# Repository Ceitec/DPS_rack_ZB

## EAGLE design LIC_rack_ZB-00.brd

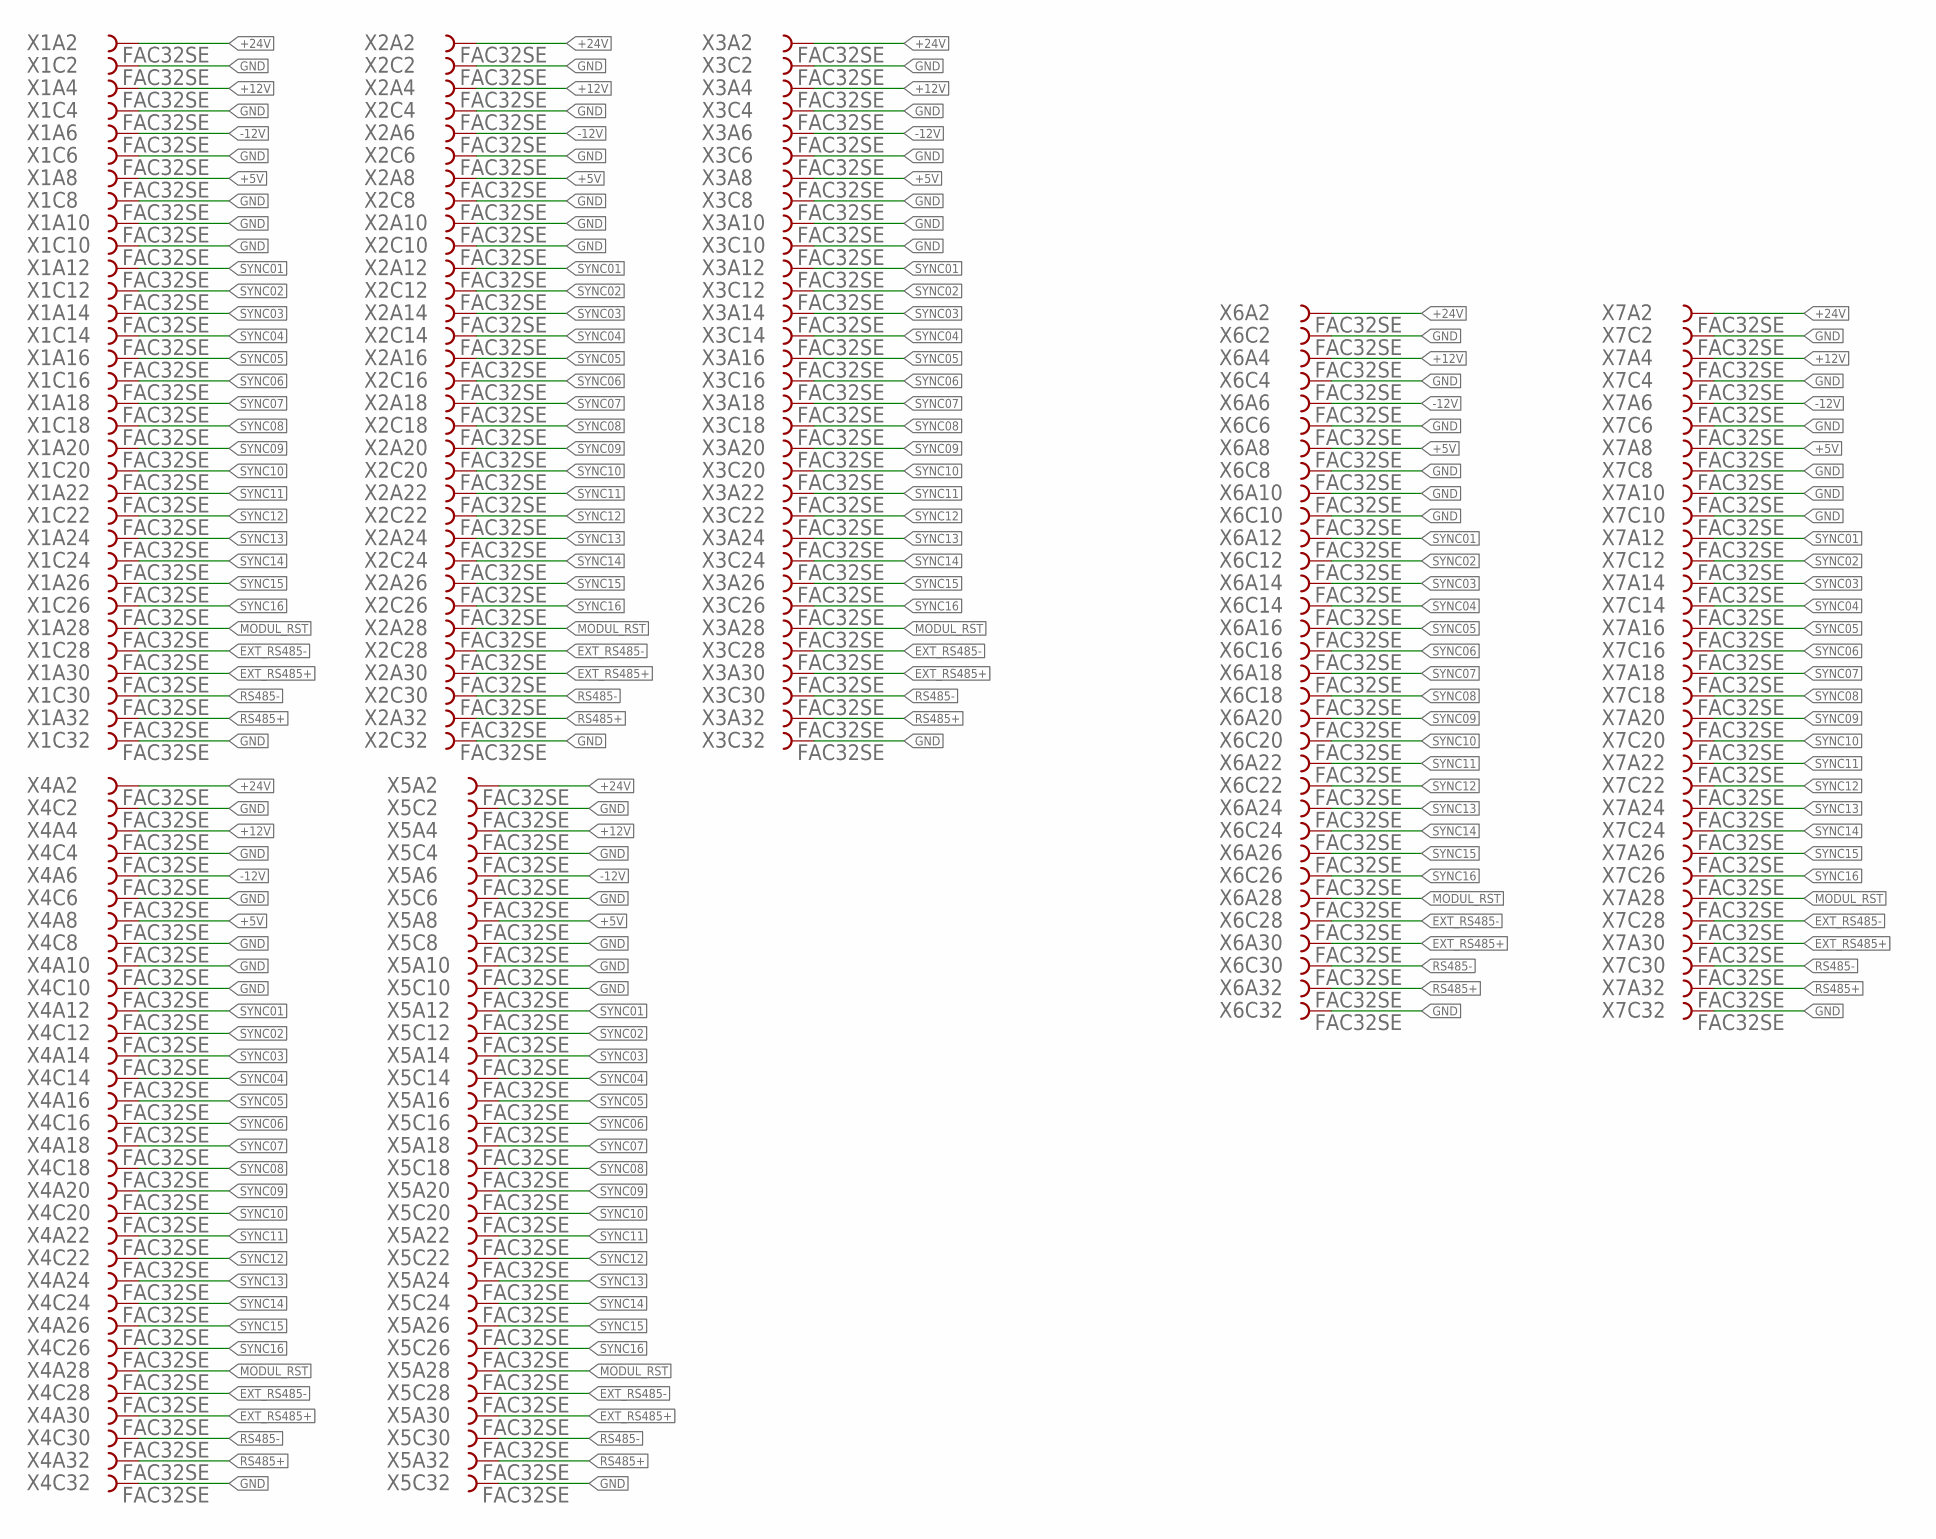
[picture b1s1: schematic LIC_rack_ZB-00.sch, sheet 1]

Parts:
X1, X2, X3, X4, X5, X6, X7: FAC32SE; FAC32S

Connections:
+5V: X1.A8, X2.A8, X3.A8, X4.A8, X5.A8, X6.A8, X7.A8; also elsewhere on the board
+12V: X1.A4, X2.A4, X3.A4, X4.A4, X5.A4, X6.A4, X7.A4; also elsewhere on the board
+24V: X1.A2, X2.A2, X3.A2, X4.A2, X5.A2, X6.A2, X7.A2; also elsewhere on the board
-12V: X1.A6, X2.A6, X3.A6, X4.A6, X5.A6, X6.A6, X7.A6; also elsewhere on the board
EXT_RS485+: X1.A30, X2.A30, X3.A30, X4.A30, X5.A30, X6.A30, X7.A30; also elsewhere on the board
EXT_RS485-: X1.C28, X2.C28, X3.C28, X4.C28, X5.C28, X6.C28, X7.C28; also elsewhere on the board
GND: X1.A10, X1.C2, X1.C4, X1.C6, X1.C8, X1.C10, X1.C32, X2.A10, X2.C2, X2.C4, X2.C6, X2.C8, X2.C10, X2.C32, X3.A10, X3.C2, X3.C4, X3.C6, X3.C8, X3.C10, X3.C32, X4.A10, X4.C2, X4.C4, X4.C6, X4.C8, X4.C10, X4.C32, X5.A10, X5.C2, X5.C4, X5.C6, X5.C8, X5.C10, X5.C32, X6.A10, X6.C2, X6.C4, X6.C6, X6.C8, X6.C10, X6.C32, X7.A10, X7.C2, X7.C4, X7.C6, X7.C8, X7.C10, X7.C32; also elsewhere on the board
MODUL_RST: X1.A28, X2.A28, X3.A28, X4.A28, X5.A28, X6.A28, X7.A28; also elsewhere on the board
RS485+: X1.A32, X2.A32, X3.A32, X4.A32, X5.A32, X6.A32, X7.A32; also elsewhere on the board
RS485-: X1.C30, X2.C30, X3.C30, X4.C30, X5.C30, X6.C30, X7.C30; also elsewhere on the board
SYNC01: X1.A12, X2.A12, X3.A12, X4.A12, X5.A12, X6.A12, X7.A12; also elsewhere on the board
SYNC02: X1.C12, X2.C12, X3.C12, X4.C12, X5.C12, X6.C12, X7.C12; also elsewhere on the board
SYNC03: X1.A14, X2.A14, X3.A14, X4.A14, X5.A14, X6.A14, X7.A14; also elsewhere on the board
SYNC04: X1.C14, X2.C14, X3.C14, X4.C14, X5.C14, X6.C14, X7.C14; also elsewhere on the board
SYNC05: X1.A16, X2.A16, X3.A16, X4.A16, X5.A16, X6.A16, X7.A16; also elsewhere on the board
SYNC06: X1.C16, X2.C16, X3.C16, X4.C16, X5.C16, X6.C16, X7.C16; also elsewhere on the board
SYNC07: X1.A18, X2.A18, X3.A18, X4.A18, X5.A18, X6.A18, X7.A18; also elsewhere on the board
SYNC08: X1.C18, X2.C18, X3.C18, X4.C18, X5.C18, X6.C18, X7.C18; also elsewhere on the board
SYNC09: X1.A20, X2.A20, X3.A20, X4.A20, X5.A20, X6.A20, X7.A20; also elsewhere on the board
SYNC10: X1.C20, X2.C20, X3.C20, X4.C20, X5.C20, X6.C20, X7.C20; also elsewhere on the board
SYNC11: X1.A22, X2.A22, X3.A22, X4.A22, X5.A22, X6.A22, X7.A22; also elsewhere on the board
SYNC12: X1.C22, X2.C22, X3.C22, X4.C22, X5.C22, X6.C22, X7.C22; also elsewhere on the board
SYNC13: X1.A24, X2.A24, X3.A24, X4.A24, X5.A24, X6.A24, X7.A24; also elsewhere on the board
SYNC14: X1.C24, X2.C24, X3.C24, X4.C24, X5.C24, X6.C24, X7.C24; also elsewhere on the board
SYNC15: X1.A26, X2.A26, X3.A26, X4.A26, X5.A26, X6.A26, X7.A26; also elsewhere on the board
SYNC16: X1.C26, X2.C26, X3.C26, X4.C26, X5.C26, X6.C26, X7.C26; also elsewhere on the board

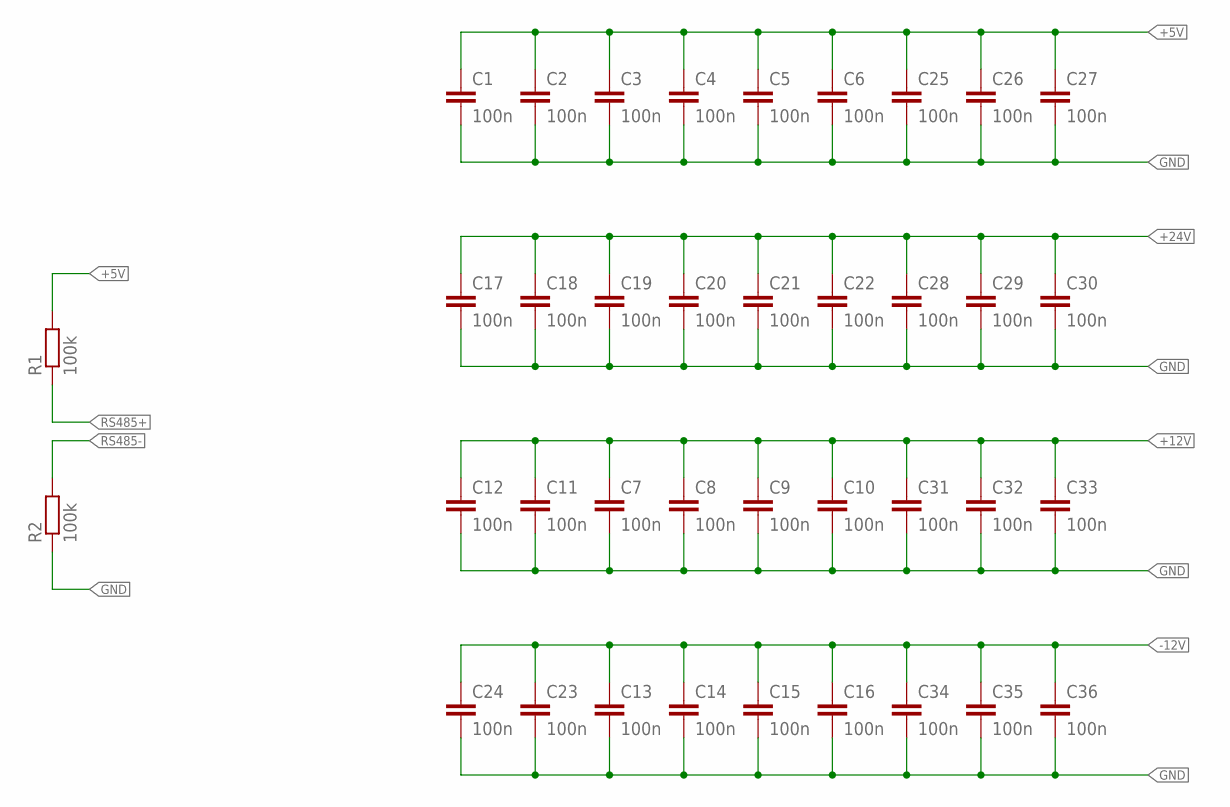
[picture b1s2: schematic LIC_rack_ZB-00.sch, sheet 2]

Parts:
C1, C2, C3, C4, C5, C6, C7, C8, C9, C10, C11, C12, C13, C14, C15, C16, C17, C18, C19, C20, C21, C22, C23, C24, C25, C26, C27, C28, C29, C30, C31, C32, C33, C34, C35, C36: 100n; C1206
R1, R2: 100k; R1206

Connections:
+5V: C1.1, C2.1, C3.1, C4.1, C5.1, C6.1, C25.1, C26.1, C27.1, R1.2; also elsewhere on the board
+12V: C7.1, C8.1, C9.1, C10.1, C11.1, C12.1, C31.1, C32.1, C33.1; also elsewhere on the board
+24V: C17.1, C18.1, C19.1, C20.1, C21.1, C22.1, C28.1, C29.1, C30.1; also elsewhere on the board
-12V: C13.1, C14.1, C15.1, C16.1, C23.1, C24.1, C34.1, C35.1, C36.1; also elsewhere on the board
GND: C1.2, C2.2, C3.2, C4.2, C5.2, C6.2, C7.2, C8.2, C9.2, C10.2, C11.2, C12.2, C13.2, C14.2, C15.2, C16.2, C17.2, C18.2, C19.2, C20.2, C21.2, C22.2, C23.2, C24.2, C25.2, C26.2, C27.2, C28.2, C29.2, C30.2, C31.2, C32.2, C33.2, C34.2, C35.2, C36.2, R2.1; also elsewhere on the board
RS485+: R1.1; also elsewhere on the board
RS485-: R2.2; also elsewhere on the board

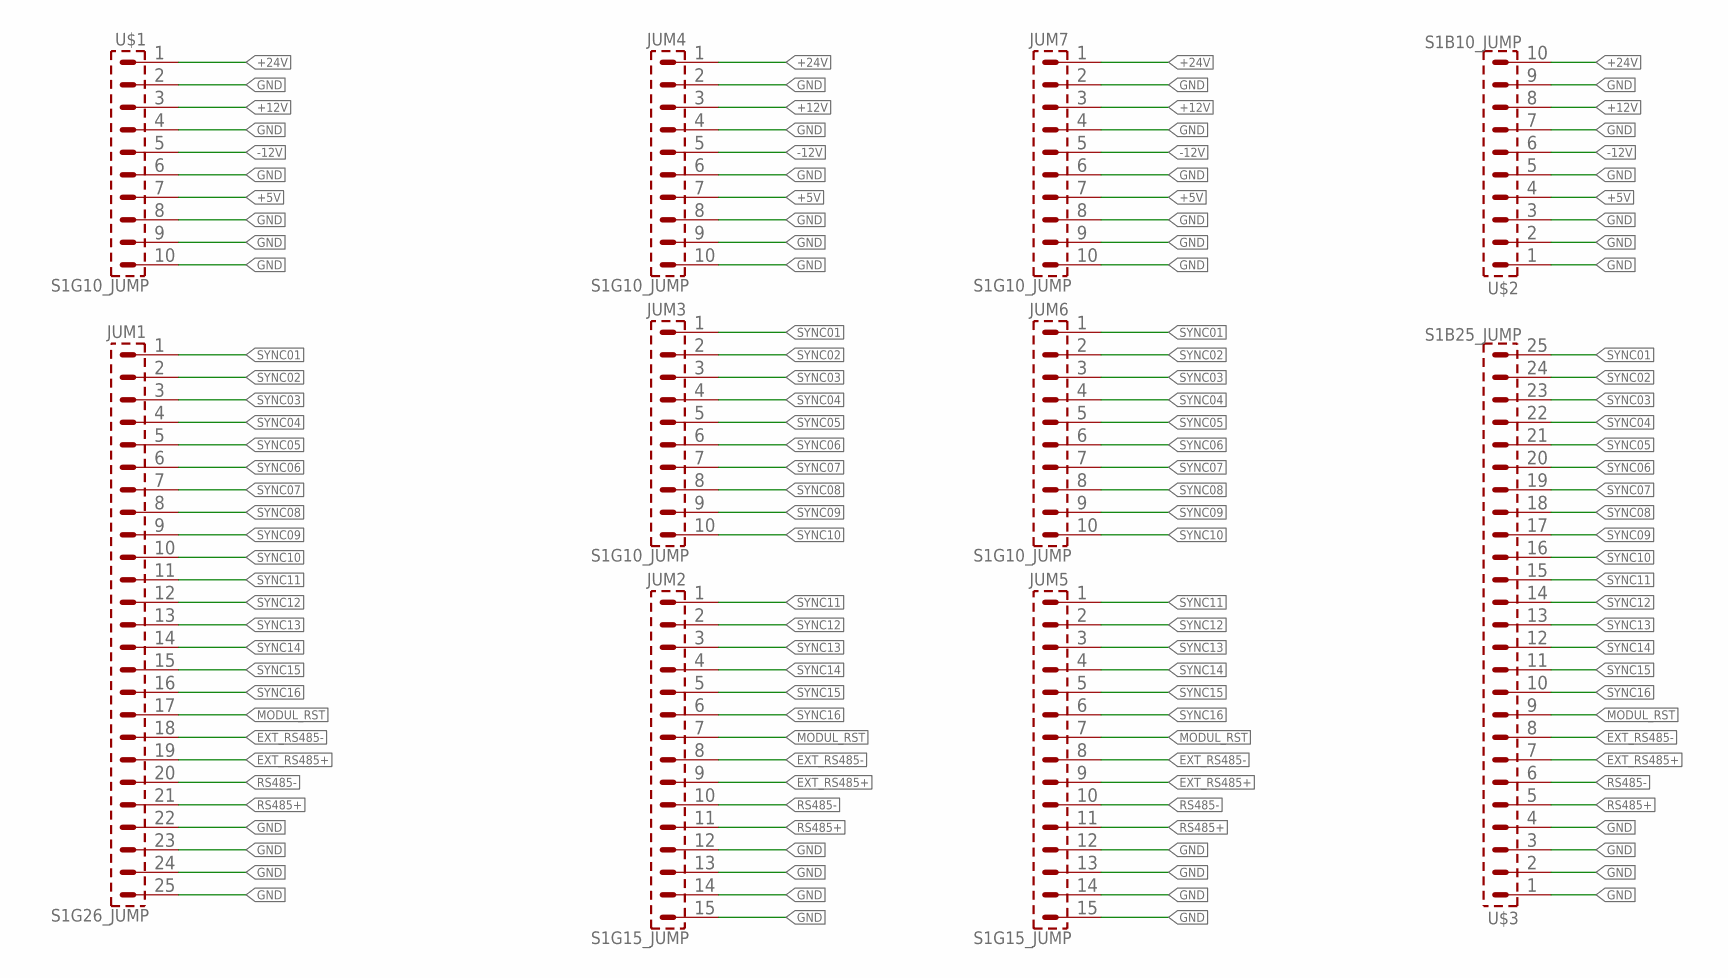
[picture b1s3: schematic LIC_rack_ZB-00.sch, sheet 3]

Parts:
JUM1: S1G26_JUMP; S1G26_JU
JUM2, JUM5: S1G15_JUMP; S1G15_JU
JUM3, JUM4, JUM6, JUM7: S1G10_JUMP; S1G10_JU
U$1: S1G10_JUMP; S1G6_JU
U$2: S1B10_JUMP; S1B10_JU
U$3: S1B25_JUMP; S1B26_JU

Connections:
+5V: JUM4.7, JUM7.7, U$1.7, U$2.4; also elsewhere on the board
+12V: JUM4.3, JUM7.3, U$1.3, U$2.8; also elsewhere on the board
+24V: JUM4.1, JUM7.1, U$1.1, U$2.10; also elsewhere on the board
-12V: JUM4.5, JUM7.5, U$1.5, U$2.6; also elsewhere on the board
EXT_RS485+: JUM1.19, JUM2.9, JUM5.9, U$3.7; also elsewhere on the board
EXT_RS485-: JUM1.18, JUM2.8, JUM5.8, U$3.8; also elsewhere on the board
GND: JUM1.22, JUM1.23, JUM1.24, JUM1.25, JUM2.12, JUM2.13, JUM2.14, JUM2.15, JUM4.2, JUM4.4, JUM4.6, JUM4.8, JUM4.9, JUM4.10, JUM5.12, JUM5.13, JUM5.14, JUM5.15, JUM7.2, JUM7.4, JUM7.6, JUM7.8, JUM7.9, JUM7.10, U$1.2, U$1.4, U$1.6, U$1.8, U$1.9, U$1.10, U$2.1, U$2.2, U$2.3, U$2.5, U$2.7, U$2.9, U$3.1, U$3.2, U$3.3, U$3.4; also elsewhere on the board
MODUL_RST: JUM1.17, JUM2.7, JUM5.7, U$3.9; also elsewhere on the board
RS485+: JUM1.21, JUM2.11, JUM5.11, U$3.5; also elsewhere on the board
RS485-: JUM1.20, JUM2.10, JUM5.10, U$3.6; also elsewhere on the board
SYNC01: JUM1.1, JUM3.1, JUM6.1, U$3.25; also elsewhere on the board
SYNC02: JUM1.2, JUM3.2, JUM6.2, U$3.24; also elsewhere on the board
SYNC03: JUM1.3, JUM3.3, JUM6.3, U$3.23; also elsewhere on the board
SYNC04: JUM1.4, JUM3.4, JUM6.4, U$3.22; also elsewhere on the board
SYNC05: JUM1.5, JUM3.5, JUM6.5, U$3.21; also elsewhere on the board
SYNC06: JUM1.6, JUM3.6, JUM6.6, U$3.20; also elsewhere on the board
SYNC07: JUM1.7, JUM3.7, JUM6.7, U$3.19; also elsewhere on the board
SYNC08: JUM1.8, JUM3.8, JUM6.8, U$3.18; also elsewhere on the board
SYNC09: JUM1.9, JUM3.9, JUM6.9, U$3.17; also elsewhere on the board
SYNC10: JUM1.10, JUM3.10, JUM6.10, U$3.16; also elsewhere on the board
SYNC11: JUM1.11, JUM2.1, JUM5.1, U$3.15; also elsewhere on the board
SYNC12: JUM1.12, JUM2.2, JUM5.2, U$3.14; also elsewhere on the board
SYNC13: JUM1.13, JUM2.3, JUM5.3, U$3.13; also elsewhere on the board
SYNC14: JUM1.14, JUM2.4, JUM5.4, U$3.12; also elsewhere on the board
SYNC15: JUM1.15, JUM2.5, JUM5.5, U$3.11; also elsewhere on the board
SYNC16: JUM1.16, JUM2.6, JUM5.6, U$3.10; also elsewhere on the board

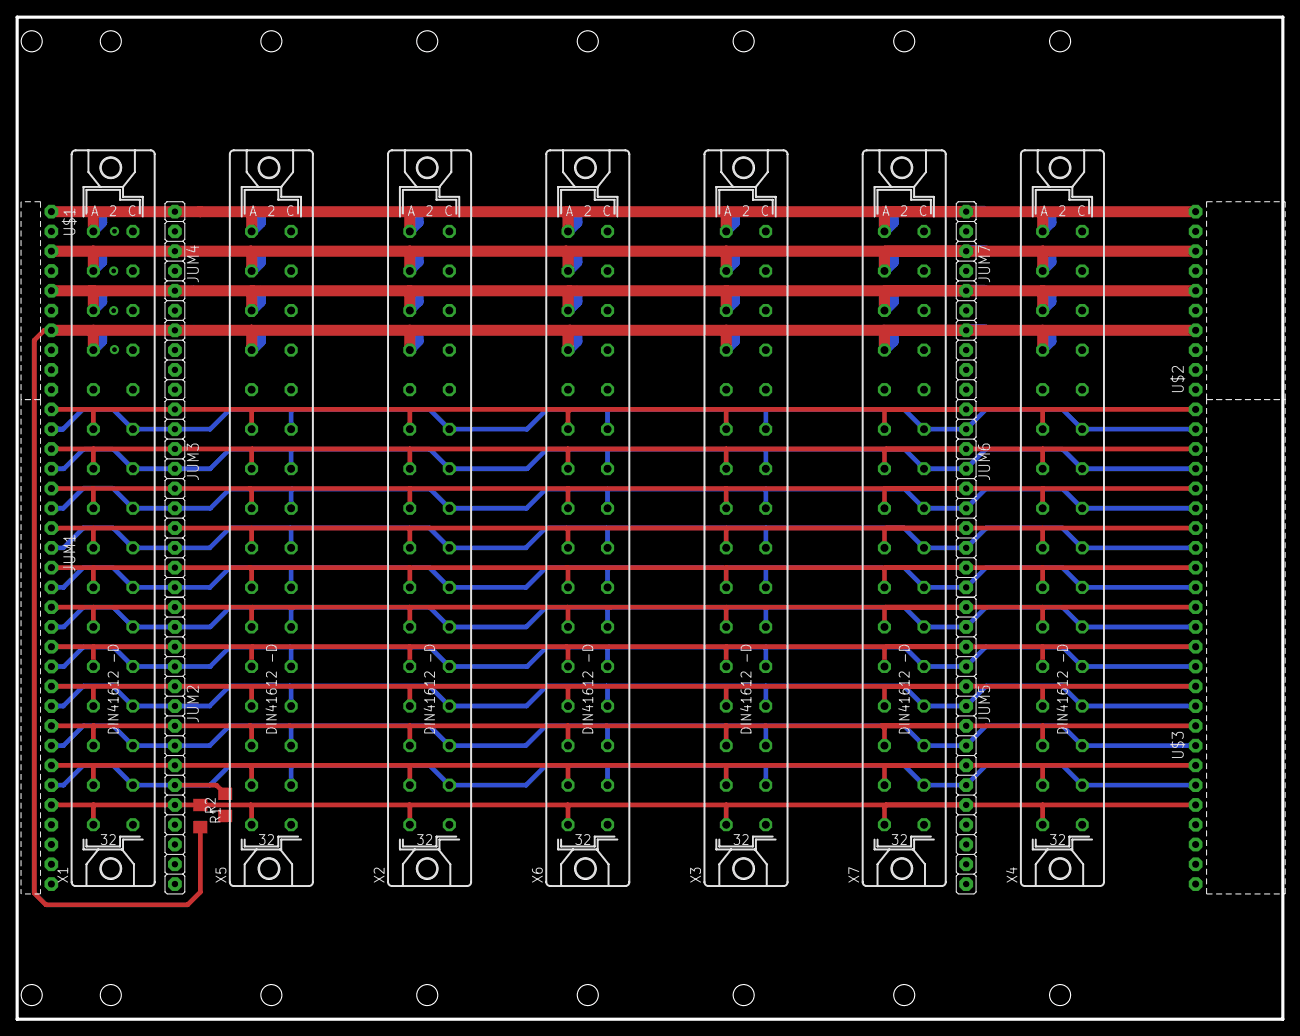
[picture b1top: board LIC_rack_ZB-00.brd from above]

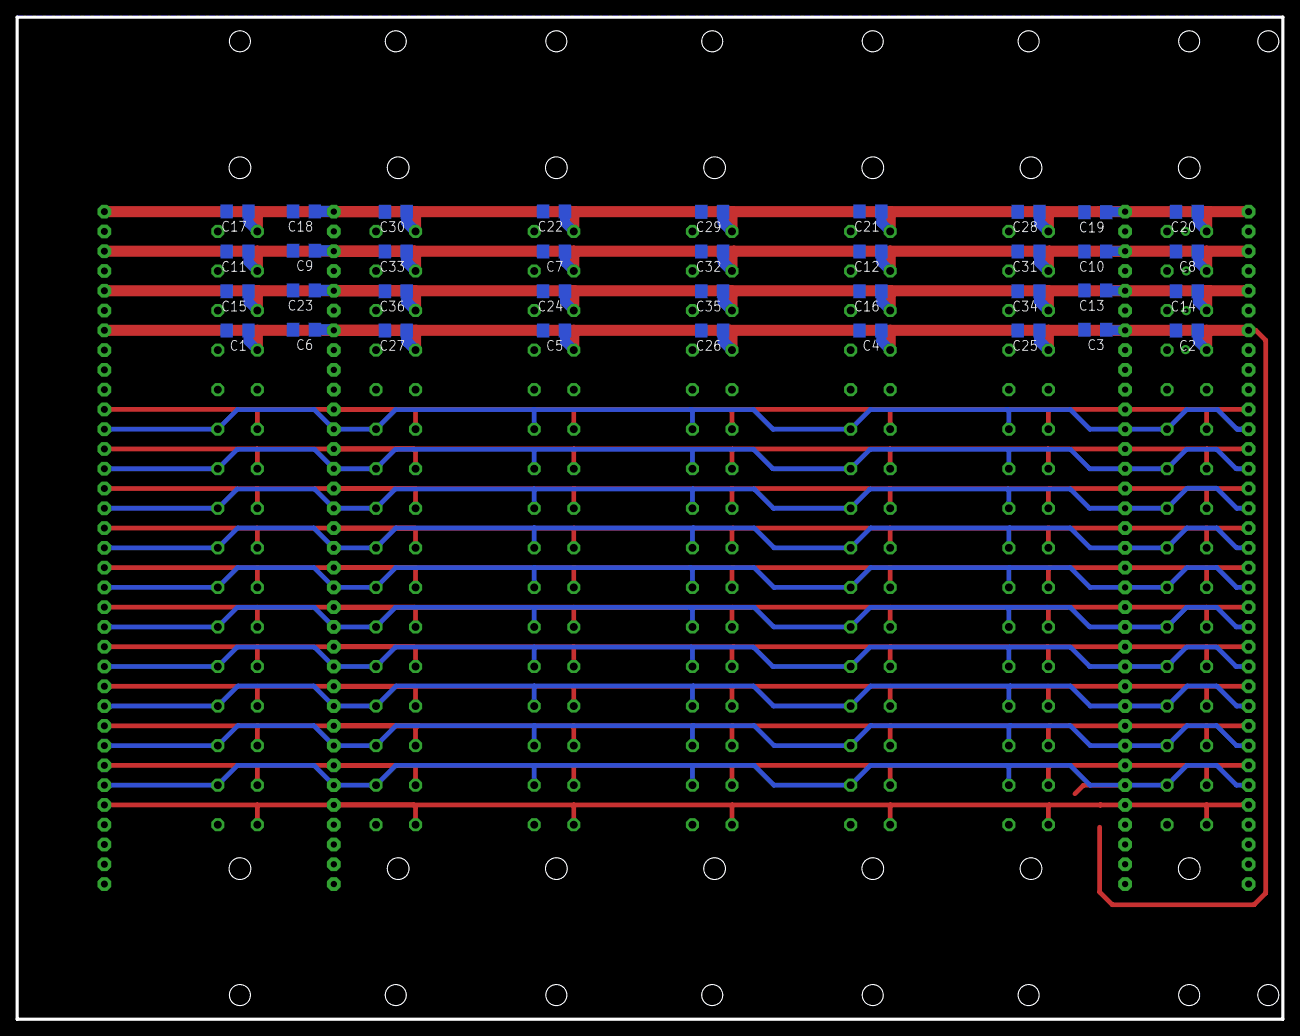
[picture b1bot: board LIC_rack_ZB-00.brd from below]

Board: 2 copper layers, 162.6 x 128.7 mm, 55 parts (36 on the bottom side), 26 nets.

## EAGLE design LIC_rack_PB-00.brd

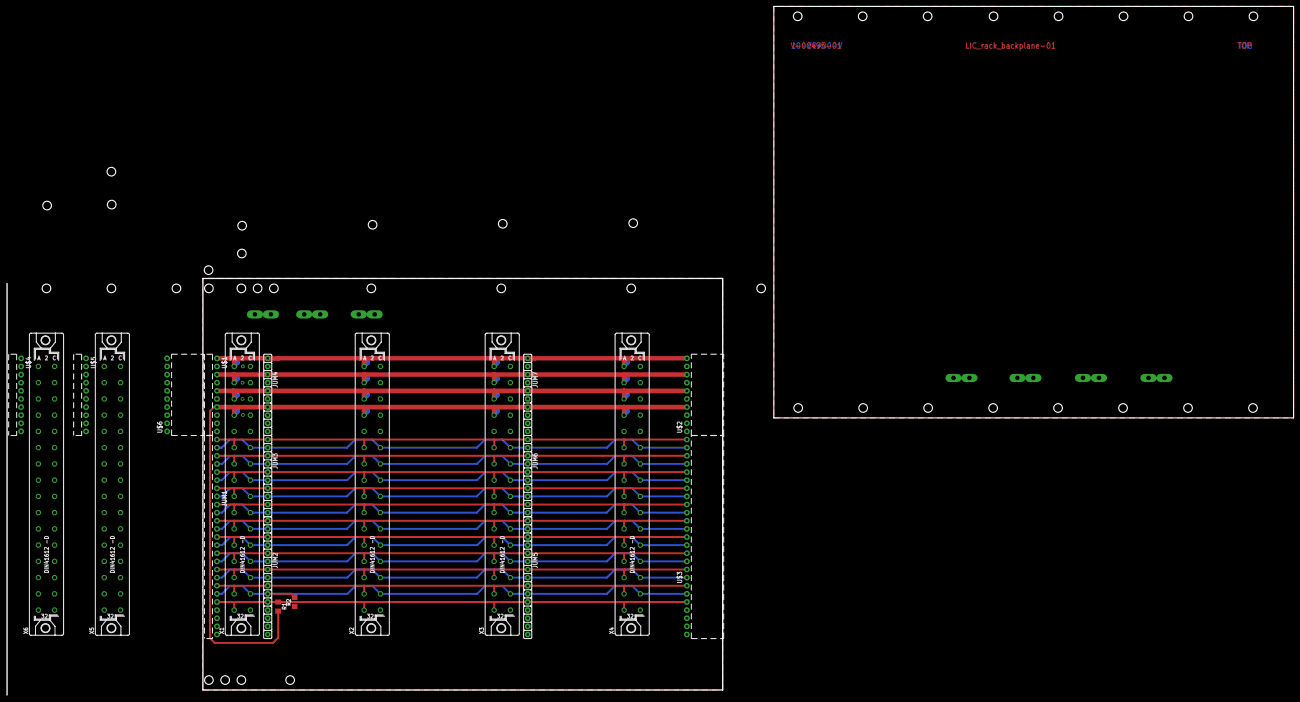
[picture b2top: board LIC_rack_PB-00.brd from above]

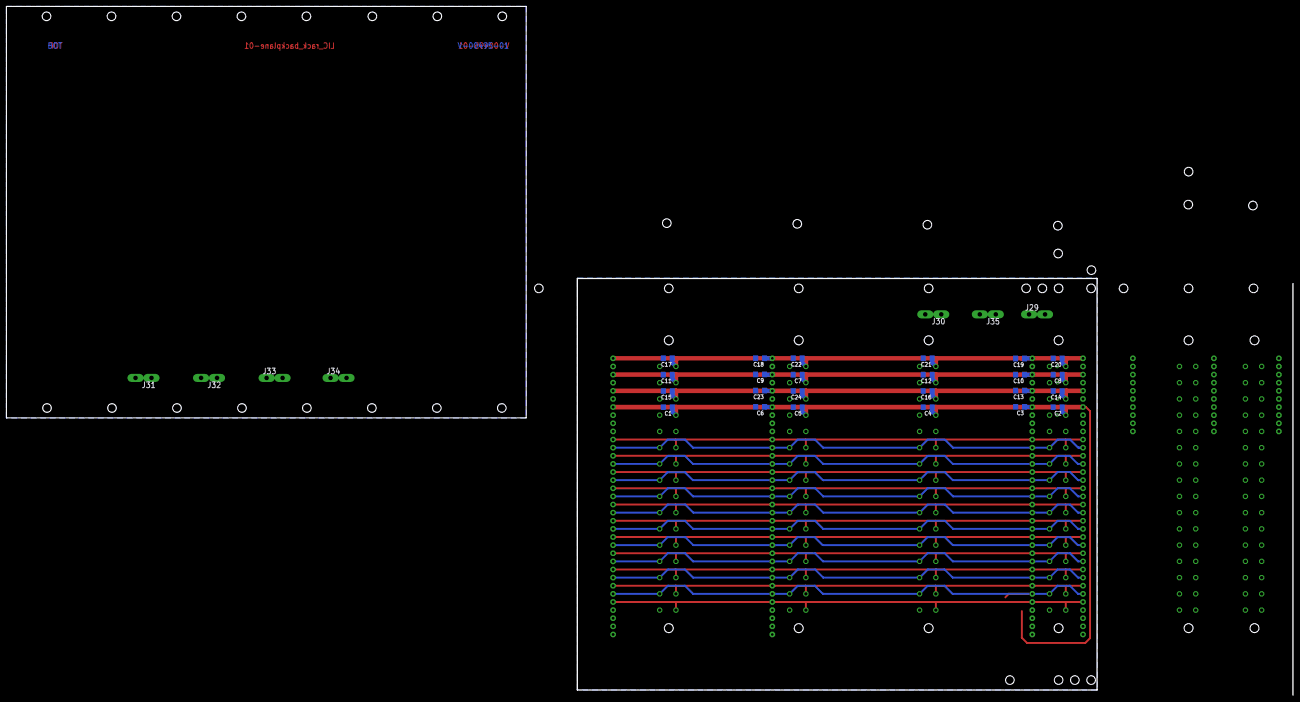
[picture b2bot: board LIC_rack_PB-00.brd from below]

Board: 2 copper layers, 162.6 x 128.7 mm, 52 parts (31 on the bottom side), 29 nets.

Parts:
C1, C2, C3, C4, C5, C6, C7, C8, C9, C10, C11, C12, C13, C14, C15, C16, C17, C18, C19, C20, C21, C22, C23, C24: 100n; C1206
J29, J30, J31, J32, J33, J34, J35: PIN2F061.100; F061.100
JUM1: S1G26_JUMP; S1G26_JU
JUM2, JUM5: S1G15_JUMP; S1G15_JU
JUM3, JUM4, JUM6, JUM7: S1G10_JUMP; S1G10_JU
R1, R2: 100k; R1206
U$1, U$4, U$5: S1G10_JUMP; S1G6_JU
U$2, U$6: S1B10_JUMP; S1B10_JU
U$3: S1B25_JUMP; S1B26_JU
X1, X2, X3, X4, X5, X6: FAC32SE; FAC32S

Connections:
+5V: C1.1, C2.1, C3.1, C4.1, C5.1, C6.1, JUM4.7, JUM7.7, R1.2, U$1.7, U$2.4, X1.A8, X2.A8, X3.A8, X4.A8
+12V: C7.1, C8.1, C9.1, C10.1, C11.1, C12.1, JUM4.3, JUM7.3, U$1.3, U$2.8, X1.A4, X2.A4, X3.A4, X4.A4
+24V: C17.1, C18.1, C19.1, C20.1, C21.1, C22.1, JUM4.1, JUM7.1, U$1.1, U$2.10, X1.A2, X2.A2, X3.A2, X4.A2
-12V: C13.1, C14.1, C15.1, C16.1, C23.1, C24.1, JUM4.5, JUM7.5, U$1.5, U$2.6, X1.A6, X2.A6, X3.A6, X4.A6
EXT_RS485+: JUM1.19, JUM2.9, JUM5.9, U$3.7, X1.A30, X2.A30, X3.A30, X4.A30
EXT_RS485-: JUM1.18, JUM2.8, JUM5.8, U$3.8, X1.C28, X2.C28, X3.C28, X4.C28
GND: C1.2, C2.2, C3.2, C4.2, C5.2, C6.2, C7.2, C8.2, C9.2, C10.2, C11.2, C12.2, C13.2, C14.2, C15.2, C16.2, C17.2, C18.2, C19.2, C20.2, C21.2, C22.2, C23.2, C24.2, JUM1.22, JUM1.23, JUM1.24, JUM1.25, JUM2.12, JUM2.13, JUM2.14, JUM2.15, JUM4.2, JUM4.4, JUM4.6, JUM4.8, JUM4.9, JUM4.10, JUM5.12, JUM5.13, JUM5.14, JUM5.15, JUM7.2, JUM7.4, JUM7.6, JUM7.8, JUM7.9, JUM7.10, R2.1, U$1.2, U$1.4, U$1.6, U$1.8, U$1.9, U$1.10, U$2.1, U$2.2, U$2.3, U$2.5, U$2.7, U$2.9, U$3.1, U$3.2, U$3.3, U$3.4, X1.A10, X1.C2, X1.C4, X1.C6, X1.C8, X1.C10, X1.C32, X2.A10, X2.C2, X2.C4, X2.C6, X2.C8, X2.C10, X2.C32, X3.A10, X3.C2, X3.C4, X3.C6, X3.C8, X3.C10, X3.C32, X4.A10, X4.C2, X4.C4, X4.C6, X4.C8, X4.C10, X4.C32
L: J29.A1, J29.A2
MODUL_RST: JUM1.17, JUM2.7, JUM5.7, U$3.9, X1.A28, X2.A28, X3.A28, X4.A28
N: J30.A1, J30.A2
PE: J31.A1, J31.A2, J32.A1, J32.A2, J33.A1, J33.A2, J34.A1, J34.A2, J35.A1, J35.A2
RS485+: JUM1.21, JUM2.11, JUM5.11, R1.1, U$3.5, X1.A32, X2.A32, X3.A32, X4.A32
RS485-: JUM1.20, JUM2.10, JUM5.10, R2.2, U$3.6, X1.C30, X2.C30, X3.C30, X4.C30
SYNC01: JUM1.1, JUM3.1, JUM6.1, U$3.25, X1.A12, X2.A12, X3.A12, X4.A12
SYNC02: JUM1.2, JUM3.2, JUM6.2, U$3.24, X1.C12, X2.C12, X3.C12, X4.C12
SYNC03: JUM1.3, JUM3.3, JUM6.3, U$3.23, X1.A14, X2.A14, X3.A14, X4.A14
SYNC04: JUM1.4, JUM3.4, JUM6.4, U$3.22, X1.C14, X2.C14, X3.C14, X4.C14
SYNC05: JUM1.5, JUM3.5, JUM6.5, U$3.21, X1.A16, X2.A16, X3.A16, X4.A16
SYNC06: JUM1.6, JUM3.6, JUM6.6, U$3.20, X1.C16, X2.C16, X3.C16, X4.C16
SYNC07: JUM1.7, JUM3.7, JUM6.7, U$3.19, X1.A18, X2.A18, X3.A18, X4.A18
SYNC08: JUM1.8, JUM3.8, JUM6.8, U$3.18, X1.C18, X2.C18, X3.C18, X4.C18
SYNC09: JUM1.9, JUM3.9, JUM6.9, U$3.17, X1.A20, X2.A20, X3.A20, X4.A20
SYNC10: JUM1.10, JUM3.10, JUM6.10, U$3.16, X1.C20, X2.C20, X3.C20, X4.C20
SYNC11: JUM1.11, JUM2.1, JUM5.1, U$3.15, X1.A22, X2.A22, X3.A22, X4.A22
SYNC12: JUM1.12, JUM2.2, JUM5.2, U$3.14, X1.C22, X2.C22, X3.C22, X4.C22
SYNC13: JUM1.13, JUM2.3, JUM5.3, U$3.13, X1.A24, X2.A24, X3.A24, X4.A24
SYNC14: JUM1.14, JUM2.4, JUM5.4, U$3.12, X1.C24, X2.C24, X3.C24, X4.C24
SYNC15: JUM1.15, JUM2.5, JUM5.5, U$3.11, X1.A26, X2.A26, X3.A26, X4.A26
SYNC16: JUM1.16, JUM2.6, JUM5.6, U$3.10, X1.C26, X2.C26, X3.C26, X4.C26

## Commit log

2015-11-10 :tada: Added .gitattributes & .gitignore files
2015-11-10 Základní Backplane
    Základní backplane vytvořená deska pro Diplomovou práci
2015-11-22 Uprava knihovny

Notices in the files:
parts and their libraries:
LIC_ALL-00: Copyright (C) PaJa 2011-2014
